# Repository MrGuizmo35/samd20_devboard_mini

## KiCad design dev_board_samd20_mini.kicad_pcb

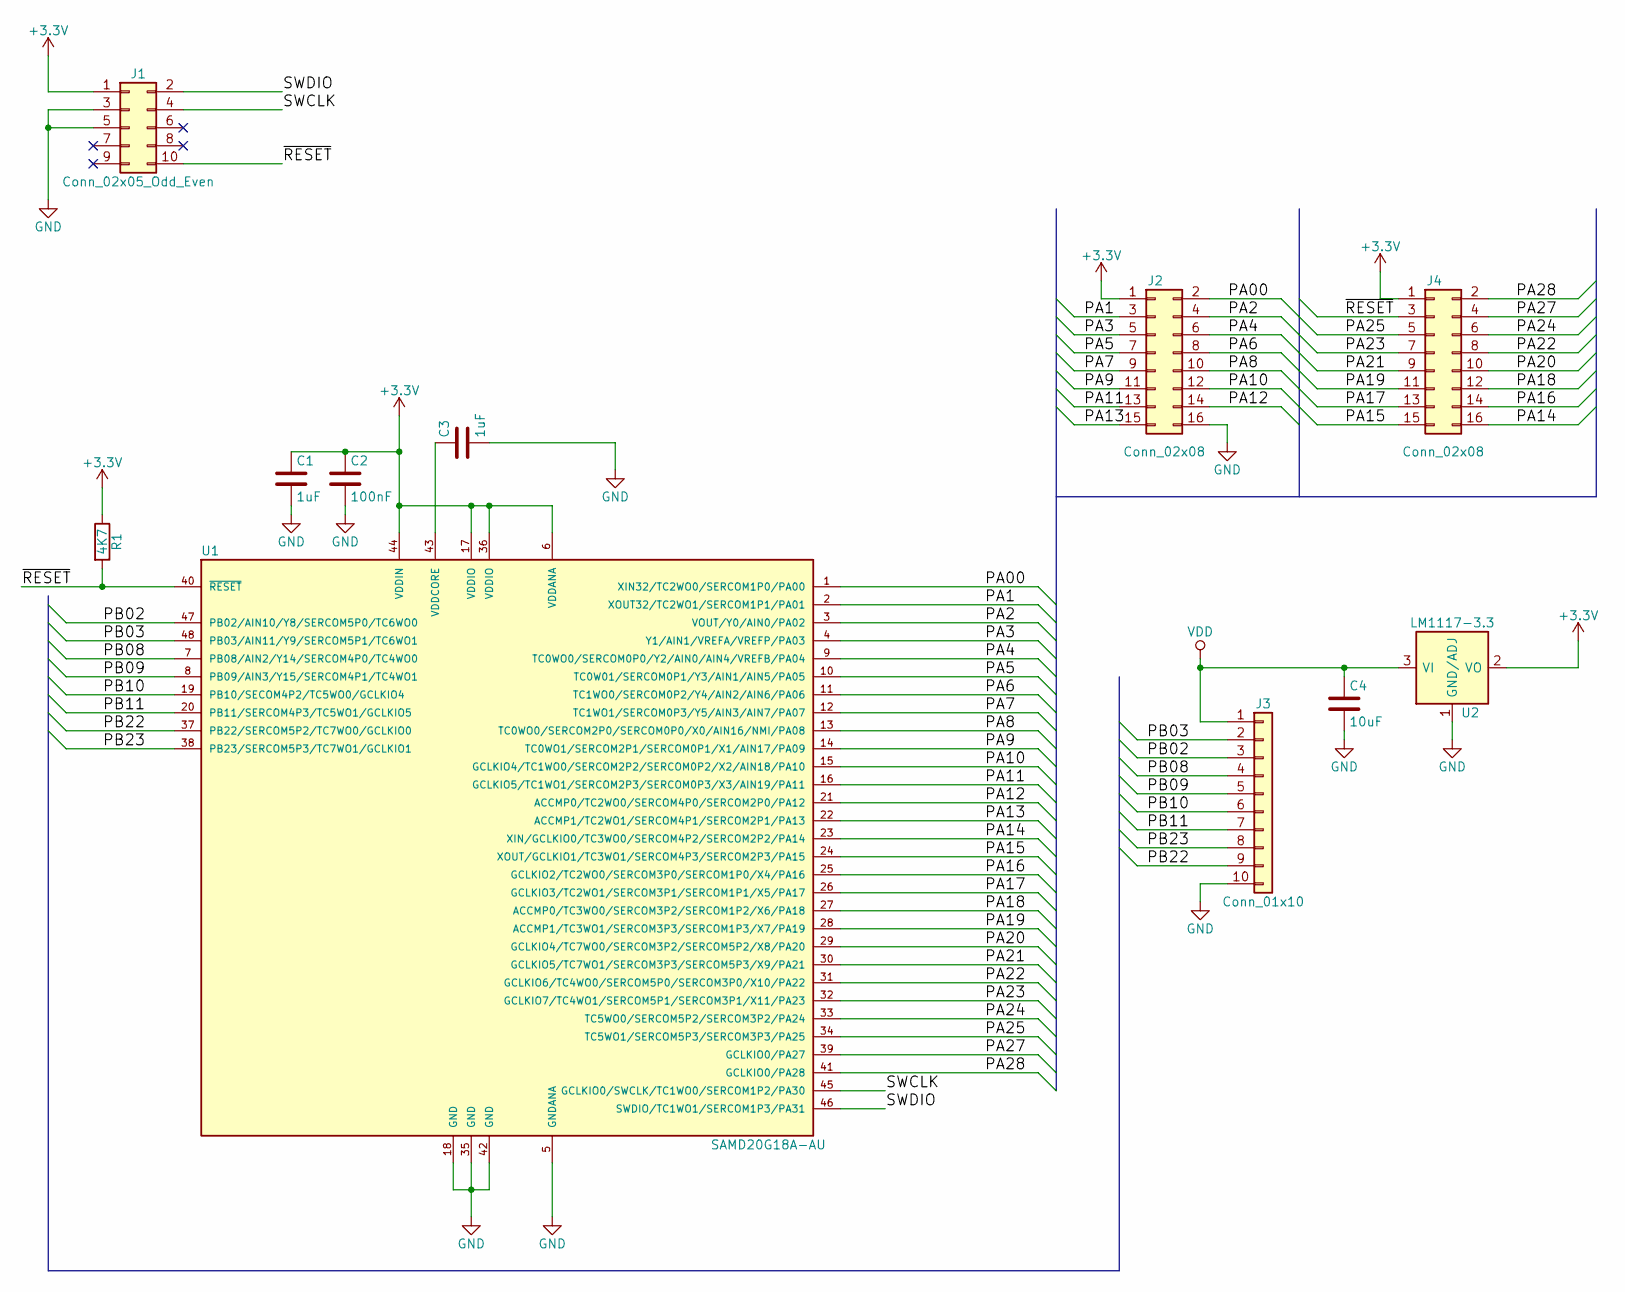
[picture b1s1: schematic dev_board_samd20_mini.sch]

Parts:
C1, C3: 1uF; C_0805
C2: 100nF; C_0805
C4: 10uF; C_0805
J1: Conn_02x05_Odd_Even; Pin_Header_Straight_2x05_Pitch1.27mm
J2, J4: Conn_02x08; Pin_Header_Straight_2x08_Pitch2.54mm
J3: Conn_01x10; Pin_Header_Straight_1x10_Pitch2.54mm
R1: 4K7; R_0805
U1: SAMD20G18A-AU; TQFP-48_7x7mm_Pitch0.5mm
U2: LM1117-3.3; SOT-223

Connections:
+3V3: C1.1, C2.1, J1.1, J2.1, J4.1, R1.1, U1.6 (VDDANA), U1.17 (VDDIO), U1.36 (VDDIO), U1.44 (VDDIN), U2.2 (VO), U2.4 (VO)
/PA00: J2.2, U1.1 (XIN32/TC2WO0/SERCOM1P0/PA00)
/PA1: J2.3, U1.2 (XOUT32/TC2WO1/SERCOM1P1/PA01)
/PA2: J2.4, U1.3 (VOUT/Y0/AIN0/PA02)
/PA3: J2.5, U1.4 (Y1/AIN1/VREFA/VREFP/PA03)
/PA4: J2.6, U1.9 (TC0WO0/SERCOM0P0/Y2/AIN0/AIN4/VREFB/PA04)
/PA5: J2.7, U1.10 (TC0W01/SERCOM0P1/Y3/AIN1/AIN5/PA05)
/PA6: J2.8, U1.11 (TC1WO0/SERCOM0P2/Y4/AIN2/AIN6/PA06)
/PA7: J2.9, U1.12 (TC1WO1/SERCOM0P3/Y5/AIN3/AIN7/PA07)
/PA8: J2.10, U1.13 (TC0WO0/SERCOM2P0/SERCOM0P0/X0/AIN16/NMI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)
/PA9: J2.11, U1.14 (TC0WO1/SERCOM2P1/SERCOM0P1/X1/AIN17/PA09)
/PA10: J2.12, U1.15 (GCLKIO4/TC1WO0/SERCOM2P2/SERCOM0P2/X2/A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)
/PA11: J2.13, U1.16 (GCLKIO5/TC1WO1/SERCOM2P3/SERCOM0P3/X3/A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)
/PA12: J2.14, U1.21 (ACCMP0/TC2WO0/SERCOM4P0/SERCOM2P0/PA12)
/PA13: J2.15, U1.22 (ACCMP1/TC2WO1/SERCOM4P1/SERCOM2P1/PA13)
/PA14: J4.16, U1.23 (XIN/GCLKIO0/TC3WO0/SERCOM4P2/SERCOM2P2/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)
/PA15: J4.15, U1.24 (XOUT/GCLKIO1/TC3WO1/SERCOM4P3/SERCOM2P3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)
/PA16: J4.14, U1.25 (GCLKIO2/TC2WO0/SERCOM3P0/SERCOM1P0/X4/P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)
/PA17: J4.13, U1.26 (GCLKIO3/TC2WO1/SERCOM3P1/SERCOM1P1/X5/P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)
/PA18: J4.12, U1.27 (ACCMP0/TC3WO0/SERCOM3P2/SERCOM1P2/X6/PA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)
/PA19: J4.11, U1.28 (ACCMP1/TC3WO1/SERCOM3P3/SERCOM1P3/X7/PA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)
/PA20: J4.10, U1.29 (GCLKIO4/TC7WO0/SERCOM3P2/SERCOM5P2/X8/P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)
/PA21: J4.9, U1.30 (GCLKIO5/TC7WO1/SERCOM3P3/SERCOM5P3/X9/P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)
/PA22: J4.8, U1.31 (GCLKIO6/TC4WO0/SERCOM5P0/SERCOM3P0/X10/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)
/PA23: J4.7, U1.32 (GCLKIO7/TC4WO1/SERCOM5P1/SERCOM3P1/X11/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)
/PA24: J4.6, U1.33 (TC5WO0/SERCOM5P2/SERCOM3P2/PA24)
/PA25: J4.5, U1.34 (TC5WO1/SERCOM5P3/SERCOM3P3/PA25)
/PA27: J4.4, U1.39 (GCLKIO0/PA27)
/PA28: J4.2, U1.41 (GCLKIO0/PA28)
/PB02: J3.3, U1.47 (PB02/AIN10/Y8/SERCOM5P0/TC6WO0)
/PB03: J3.2, U1.48 (PB03/AIN11/Y9/SERCOM5P1/TC6WO1)
/PB08: J3.4, U1.7 (PB08/AIN2/Y14/SERCOM4P0/TC4WO0)
/PB09: J3.5, U1.8 (PB09/AIN3/Y15/SERCOM4P1/TC4WO1)
/PB10: J3.6, U1.19 (PB10/SECOM4P2/TC5WO0/GCLKIO4)
/PB11: J3.7, U1.20 (PB11/SERCOM4P3/TC5WO1/GCLKIO5)
/PB22: J3.9, U1.37 (PB22/SERCOM5P2/TC7WO0/GCLKIO0)
/PB23: J3.8, U1.38 (PB23/SERCOM5P3/TC7WO1/GCLKIO1)
/SWCLK: J1.4, U1.45 (GCLKIO0/SWCLK/TC1WO0/SERCOM1P2/PA30)
/SWDIO: J1.2, U1.46 (SWDIO/TC1WO1/SERCOM1P3/PA31)
/~RESET: J1.10, J4.3, R1.2, U1.40 (~RESET~)
GND: C1.2, C2.2, C3.2, C4.2, J1.3, J1.5, J2.16, J3.10, U1.5 (GNDANA), U1.18 (GND), U1.35 (GND), U1.42 (GND), U2.1 (GND/ADJ)
unnamed: C3.1, U1.43 (VDDCORE)
VDD: C4.1, J3.1, U2.3 (VI)

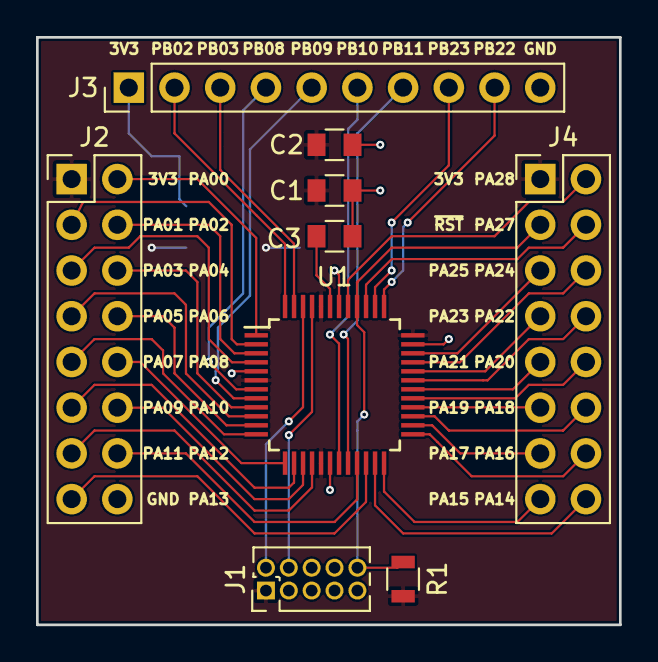
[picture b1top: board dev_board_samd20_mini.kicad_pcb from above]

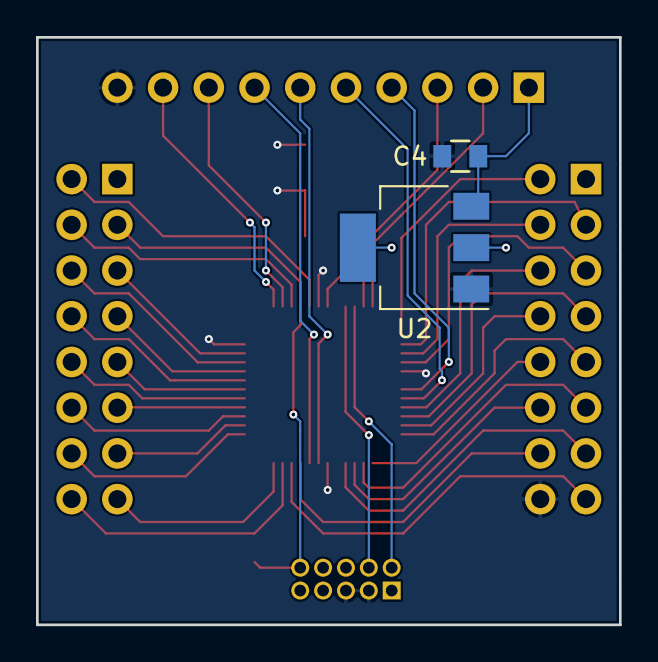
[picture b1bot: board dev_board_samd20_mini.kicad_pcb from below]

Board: 2 copper layers, 32.4 x 32.6 mm, 11 parts (2 on the bottom side), 43 nets.

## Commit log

2018-03-12 added cache lib
2018-03-12 Réduction de la taille de la carte
